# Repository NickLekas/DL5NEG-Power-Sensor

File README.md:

# DL5NEG Power Sensor
A PCB layout of the DL5NEG 6 GHz power meter

http://www.dl5neg.de/diodesensor/diodesensor.html

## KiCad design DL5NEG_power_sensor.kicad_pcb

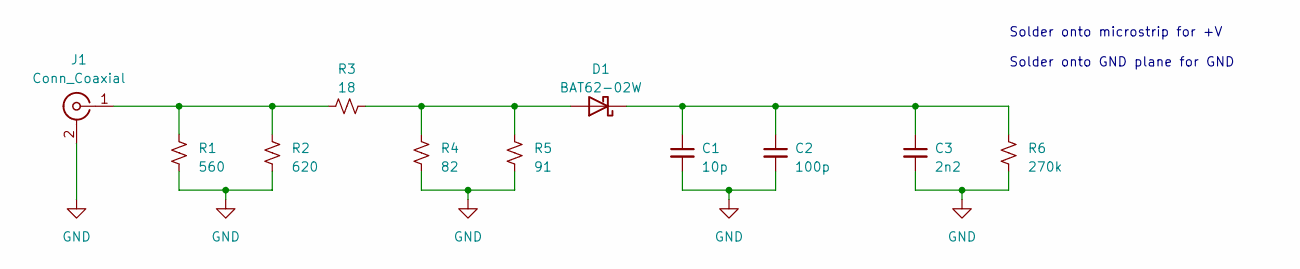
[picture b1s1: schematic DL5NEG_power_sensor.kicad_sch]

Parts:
C1: 10p; C_1206_3216Metric
C2: 100p; C_1206_3216Metric
C3: 2n2; C_1206_3216Metric
D1: BAT62-02W; D_SOD-523
J1: Conn_Coaxial; SMA_Amphenol_132289_EdgeMount
R1: 560; R_1206_3216Metric
R2: 620; R_1206_3216Metric
R3: 18; R_1206_3216Metric
R4: 82; R_1206_3216Metric
R5: 91; R_1206_3216Metric
R6: 270k; R_1206_3216Metric

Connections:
/Power_out: C1.1, C2.1, C3.1, D1.1 (K), R6.1
/RF in: J1.1 (In), R1.1, R2.1, R3.1
/RF_2: D1.2 (A), R3.2, R4.1, R5.1
GND: C1.2, C2.2, C3.2, J1.2 (Ext), R1.2, R2.2, R4.2, R5.2, R6.2

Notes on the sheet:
Solder onto microstrip for +V Solder onto GND plane for GND

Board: 2 copper layers, 11 parts (0 on the bottom side), 4 nets, no tracks yet.

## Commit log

2023-06-05 Initial commit with board layout mostly done
